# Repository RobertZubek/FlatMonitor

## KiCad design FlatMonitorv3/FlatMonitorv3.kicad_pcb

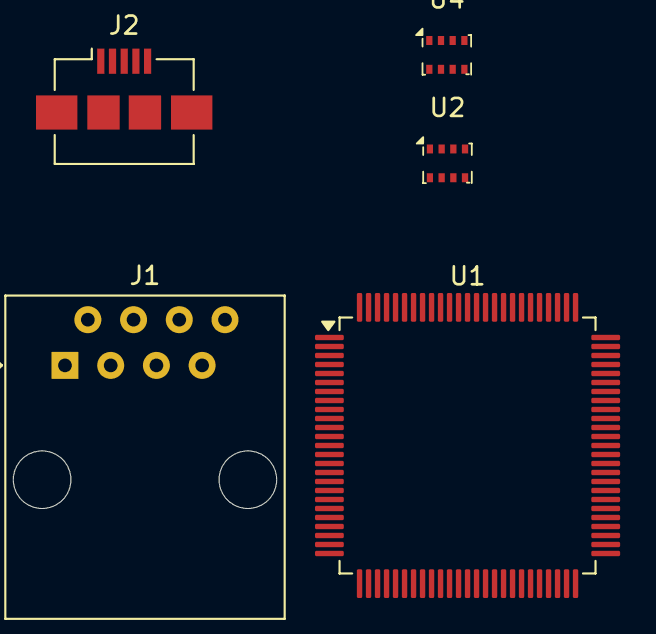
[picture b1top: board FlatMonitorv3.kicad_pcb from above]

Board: 2 copper layers, 5 parts (0 on the bottom side), 5 nets, no tracks yet.

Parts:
J1: RJ45; RJ45_Amphenol_54602-x08_Horizontal
J2: USB_B_Micro; USB_Micro-B_Amphenol_10104110_Horizontal
U1: STM32F107VCTx; LQFP-100_14x14mm_P0.5mm
U2, U4: BMP280; Bosch_LGA-8_2x2.5mm_P0.65mm_ClockwisePinNumbering

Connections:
unnamed: U1.10 (VSS), U1.27 (VSS), U1.49 (VSS), U1.74 (VSS), U1.99 (VSS)
unnamed: U2.2 (CSB), U4.2 (CSB)
unnamed: U2.4 (SCK), U4.4 (SCK)
unnamed: U2.3 (SDI), U4.3 (SDI)
unnamed: U2.5 (SDO), U4.5 (SDO)

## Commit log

2024-03-16 init
2024-03-17 buttons
2024-03-17 window name
2024-03-18 working on plots
2024-03-18 plot script ready
2024-03-18 Chart and SerialPort libs added
2024-03-18 Fight with charts
2024-03-19 Chart displayed
2024-03-19 Chart changing with button
2024-04-11 PCB in progress
2024-04-11 firmware init
